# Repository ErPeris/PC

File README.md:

# Driver per 3 servomotori: progetto KiCad, due varianti

> Nel repository c'è anche la **scheda di test con Arduino Nano** (progetto 3): è nella cartella [`Scheda_Test_Arduino/`](Scheda_Test_Arduino/README.md), che ha il suo README.

Il circuito prende l'alimentazione da una batteria LiPo 2S (7.4 V), la abbassa a 5 V per i servo e porta i tre segnali PWM del microcontrollore da 3.3 V a livello 5 V con un LM324. Tutti i componenti sono a foro passante (THT).

| Cartella | Regolatore | File |
|---|---|---|
| `Variante_A_LDO/` | lineare LM7805 (TO-220) + diodo di protezione 1N4007 | schema `Servo_Driver_A_LDO.kicad_sch`, PCB `Servo_Driver_A_LDO.kicad_pcb`, anteprime `Servo_Driver_A_LDO.pdf` e `Servo_Driver_A_LDO_PCB.pdf` |
| `Variante_B_Buck/` | switching LM2596T-5.0 (TO-220-5) con componenti discreti | schema `Servo_Driver_B_Buck.kicad_sch`, PCB `Servo_Driver_B_Buck.kicad_pcb`, anteprime `Servo_Driver_B_Buck.pdf` e `Servo_Driver_B_Buck_PCB.pdf` |

Ogni cartella è un progetto KiCad autonomo: si apre con il file `.kicad_pro`. I file sono stati creati con KiCad 7 e si aprono in KiCad 9, che li converte al nuovo formato al primo salvataggio. Al primo salvataggio KiCad 9 può avvisare che il file viene aggiornato: va bene.

## Il PCB

- **Scheda**: 80 × 60 mm, 2 strati, 4 fori di fissaggio M3 negli angoli.
- **Massa**: un piano di massa (GND) su entrambe le facce collega tutti i pin di massa.
- **Piste di potenza**: +BATT, +5V verso i servo e, nella variante B, il nodo di commutazione SW sono tracciate a mano, larghe 1.5 mm.
- **Segnali**: sbrogliati con l'autorouter Freerouting. Le piste sono larghe 0.4 mm e il resto della +5V 0.8 mm, con distanze minime di 0.3 mm.
- **Classi di net**: sono nel `.kicad_pro`. La classe `Power` comprende GND, +BATT, +5V e SW.
- **Disposizione**:
  - in alto, la batteria (J1) a sinistra e lo stadio di alimentazione;
  - in basso a sinistra, l'ingresso PWM (J2) con le resistenze;
  - al centro, l'LM324 su zoccolo DIP-14;
  - a destra, le tre uscite servo (J3–J5).
- **Serigrafia**: polarità della batteria (+/−), pin del connettore PWM (G, 1, 2, 3) e pin di ogni servo (G, +, S).
- **DRC**: senza errori e senza pad scollegati.

Il file `.kicad_dru` contiene una sola regola: accetta un solo raggio di collegamento termico per faccia, perché i pad di massa sono collegati al piano su tutte e due le facce. Senza questa regola il DRC segnala un pad di R5.

**Prima di mandare la scheda in produzione:**
1. In KiCad 9 lanciare il controllo regole elettriche (ERC) sullo schema e il controllo regole di progettazione (DRC) sul PCB, con la verifica di coerenza tra schema e PCB attiva.
2. Controllare le impronte di L1 e dei condensatori elettrolitici sui componenti acquistati (diametro e passo dei piedini).
3. Nella variante A lasciare spazio al dissipatore dietro la linguetta di U1, verso il bordo superiore.
4. Se il PCB è stato modificato, rigenerare i Gerber (vedi sotto).

Per modificare il PCB a mano conviene ricaricare le zone di massa con il tasto **B** dopo ogni modifica.

## File per ordinare le schede

Nella cartella `produzione/` ci sono:

| File | Contenuto |
|---|---|
| `Gerber_Servo_Driver_A_LDO.zip` | Gerber e forature della variante A, da caricare così com'è sul sito del produttore |
| `Gerber_Servo_Driver_B_Buck.zip` | Gerber e forature della variante B |
| `Progetto_KiCad_Driver_3_Servo.zip` | progetto KiCad completo delle due varianti (schemi, PCB, regole, PDF, Gerber, README) |
| `Gerber_Scheda_Test_Arduino.zip` | Gerber e forature della scheda di test con Arduino Nano |
| `Progetto_KiCad_Scheda_Test_Arduino.zip` | progetto KiCad completo della scheda di test, con lo sketch di prova |

Ogni zip Gerber contiene:
- rame lato componenti e lato saldature (`.gtl`, `.gbl`);
- maschera di saldatura (`.gts`, `.gbs`);
- serigrafia (`.gto`, `.gbo`);
- contorno della scheda (`.gm1`);
- forature metallizzate e non metallizzate (`-PTH.drl`, `-NPTH.drl`, Excellon in mm);
- il file di job (`.gbrjob`).

**Dati da inserire nell'ordine** (JLCPCB, PCBWay e simili):

| Parametro | Valore |
|---|---|
| Strati | 2 |
| Dimensioni | 80 × 60 mm |
| Spessore | 1.6 mm |
| Rame | 1 oz |
| Pista minima / distanza minima | 0.4 mm / 0.3 mm |
| Foro minimo | 0.4 mm (via) |
| Finitura | HASL |
| Colore | a piacere |

Questi valori rientrano nelle opzioni standard di tutti i produttori economici.

**Per rigenerare i Gerber dopo una modifica**, in KiCad 9 dall'editor PCB:
1. Usare **File → Fabbricazione → Gerber**. Strati da includere: F.Cu, B.Cu, F.Silkscreen, B.Silkscreen, F.Mask, B.Mask, Edge.Cuts.
2. Nella stessa finestra usare **Genera file di foratura**: Excellon, millimetri, PTH e NPTH separati.
3. Comprimere i file in uno zip.

Da riga di comando:

```sh
kicad-cli pcb export gerbers -o gerber/ --layers F.Cu,B.Cu,F.SilkS,B.SilkS,F.Mask,B.Mask,Edge.Cuts \
    --exclude-value --subtract-soldermask Servo_Driver_A_LDO.kicad_pcb
kicad-cli pcb export drill -o gerber/ --format excellon --excellon-units mm --excellon-separate-th \
    Servo_Driver_A_LDO.kicad_pcb
```

## Parte comune alle due varianti

| Rif. | Valore | Impronta | Funzione |
|---|---|---|---|
| J1 | JST-PH 2 pin | `JST_PH_B2B-PH-K_1x02_P2.00mm_Vertical` | ingresso batteria (1 = +, 2 = GND) |
| C1 | 100 µF 16 V elettrolitico | `CP_Radial_D6.3mm_P2.50mm` | filtro in parallelo all'ingresso |
| J2 | header 1x4 2.54 mm | `PinHeader_1x04_P2.54mm_Vertical` | dal microcontrollore: 1 = GND, 2/3/4 = PWM1/2/3 a 3.3 V |
| U2 | LM324 | `DIP-14_W7.62mm` | 3 comparatori (U2A, U2B, U2C) come level shifter |
| R1 | 22 kΩ | `R_Axial_DIN0207…` | partitore di riferimento (lato +5 V) |
| R2 | 10 kΩ | `R_Axial_DIN0207…` | partitore di riferimento (lato GND) |
| C2 | 100 nF | `C_Disc_D5.0mm…` | filtro sulla tensione di riferimento VREF |
| R3, R4, R5 | 100 kΩ | `R_Axial_DIN0207…` | pull-down sugli ingressi PWM |
| C3 | 100 nF | `C_Disc_D5.0mm…` | disaccoppiamento alimentazione LM324 (vicino al pin 4) |
| J3, J4, J5 | header 1x3 2.54 mm | `PinHeader_1x03_P2.54mm_Vertical` | uscite servo: 1 = GND, 2 = +5 V, 3 = PWM 5 V |
| H1–H4 | foro M3 | `MountingHole_3.2mm_M3` | fissaggio della scheda |

**Come funziona il level shifter.** Il partitore R1/R2 genera VREF = 5 V × 10k / (22k + 10k) ≈ 1.56 V, collegata agli ingressi invertenti (−) di U2A, U2B e U2C. Ogni PWM a 3.3 V entra nell'ingresso non invertente (+). Con il PWM a 3.3 V (sopra la soglia) l'uscita va alta, con il PWM a 0 V va bassa. La quarta sezione, U2D, non è usata: è collegata come inseguitore con IN+ a massa, così non oscilla.

## Variante A: regolatore lineare LDO

| Rif. | Valore | Impronta | Funzione |
|---|---|---|---|
| U1 | LM7805 | `TO-220-3_Vertical` | regolatore 5 V (1 = IN, 2 = GND, 3 = OUT) |
| D1 | 1N4007 | `D_DO-41_SOD81_P10.16mm_Horizontal` | antiparallelo: catodo su IN, anodo su OUT |
| C4 | 330 nF | `C_Disc_D5.0mm…` | condensatore d'ingresso consigliato dal datasheet del 7805 |
| C5 | 100 nF | `C_Disc_D5.0mm…` | condensatore d'uscita consigliato dal datasheet |
| C6 | 100 µF 10 V elettrolitico | `CP_Radial_D6.3mm_P2.50mm` | riserva per i picchi di corrente dei servo |

## Variante B: buck converter LM2596-5.0

| Rif. | Valore | Impronta | Funzione |
|---|---|---|---|
| U1 | LM2596T-5.0 | `TO-220-5_P3.4x3.7mm_StaggerOdd_Lead3.8mm_Vertical` | 1 = VIN, 2 = OUT, 3 = GND, 4 = FEEDBACK, 5 = ON/OFF |
| C4 | 100 µF 16 V elettrolitico | `CP_Radial_D8.0mm_P3.50mm` | condensatore d'ingresso sul pin VIN |
| D1 | 1N5822 (Schottky 3 A) | `D_DO-201AD_P15.24mm_Horizontal` | tra OUT (catodo) e GND (anodo) |
| L1 | 33 µH, ≥ 3 A | `L_Radial_D12.0mm_P5.00mm_Fastron_11P` | induttore sulla linea d'uscita |
| C5 | 220 µF 10 V low-ESR | `CP_Radial_D8.0mm_P3.50mm` | condensatore d'uscita sui 5 V |

La specifica chiede l'**LM2596S**-5.0, che esiste solo in contenitore SMD (TO-263). Visto che la scheda è tutta a foro passante, ho usato l'**LM2596T**-5.0: è lo stesso integrato in contenitore TO-220-5, con gli stessi pin. Va comprata la versione con i piedini sfalsati per il montaggio verticale. Se il professore vuole proprio la versione "S", basta cambiare simbolo e impronta di U1.

Il pin FEEDBACK (4) è collegato ai 5 V dopo l'induttore. Sul PCB la pista passa sul lato inferiore fino al pin 2 di L1. Il pin ON/OFF (5) va a GND, altrimenti il regolatore resta spento: la specifica non lo nomina, ma è necessario.

## Cose da sapere (da riportare anche nella relazione)

1. **L'LM324 a 5 V non arriva a 5 V in uscita.** Non è rail-to-rail: con alimentazione a 5 V l'uscita alta arriva a circa 3.5–3.8 V. Ai servo basta (accettano già segnali da 3.3 V), ma non sono 5 V pieni. Per averli si può montare un **MCP6004** o un **LMV324** nello stesso zoccolo DIP-14: hanno lo stesso pinout, quindi schema e PCB non cambiano.
2. **LM7805 e batteria 2S.** Il 7805 ha bisogno di circa 2 V di margine, quindi sotto ~7 V di batteria l'uscita scende sotto 5 V, e una LiPo 2S va da 8.4 V (carica) a ~6.4 V (scarica). L'**LM2940-5.0** ha lo stesso pinout TO-220 e un dropout di circa 0.5 V.
3. **Calore nella variante A.** Il regolatore lineare dissipa (Vin − 5 V) × I: con 7.4 V e 1 A sono circa 2.4 W, quindi serve un dissipatore sul TO-220. Il 7805 eroga al massimo ~1.5 A. Tre servo che si muovono insieme possono superarlo (ogni SG90 in stallo assorbe ~0.7 A, i servo più grandi anche 2 A). La variante B arriva a 3 A con molto meno calore.
4. **Layout della variante B.** L'anello C4 → U1 → D1 → L1 → C5 è tenuto corto, con il piano di massa sotto. L'impronta di L1 è indicativa: va controllata sul componente acquistato.
5. **Polarità della batteria.** Su J1 il pin 1 è il + e il pin 2 è la massa, come indicato sulla serigrafia. I connettori JST-PH delle LiPo non hanno tutti la stessa polarità: va controllata prima del primo collegamento. Non è prevista una protezione contro l'inversione di polarità.
6. **Aggiunte rispetto alla specifica.** R3–R5 (pull-down), C2 (filtro di VREF), C3 (disaccoppiamento), i fori di fissaggio e, nella variante A, C4–C6 non sono richiesti dalla specifica. Sono pratica comune e si possono togliere senza cambiare il funzionamento base.

## Rigenerare i file

Gli schemi e i PCB sono stati generati dagli script in `tools/`, che servono solo a ricrearli da zero. Per modificarli basta lavorare direttamente in KiCad. Rigenerando, le modifiche fatte a mano vanno perse.

```sh
python3 tools/genera_schemi.py      # schemi (.kicad_sch)
kicad-cli sch export netlist --format kicadxml -o A.xml Variante_A_LDO/Servo_Driver_A_LDO.kicad_sch
python3 tools/verifica_netlist.py A A.xml   # confronta i collegamenti con la specifica
FREEROUTING_JAR=freerouting-2.4.1-executable.jar JAVA=java-25 python3 tools/genera_pcb.py   # PCB
```

`genera_pcb.py` usa il modulo Python `pcbnew` di KiCad 7 e [Freerouting](https://freerouting.app) 2.4.1, che richiede Java 25.

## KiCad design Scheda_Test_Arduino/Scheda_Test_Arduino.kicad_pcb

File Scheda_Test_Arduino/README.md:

# Scheda di test con Arduino Nano

Scheda con un Arduino Nano come controllo, collegato a:
- un modulo BME280 (temperatura, umidità, pressione);
- un buzzer;
- un servomotore.

Un interruttore accende tutta la scheda e un LED si accende quando l'interruttore è su ON. Tutti i componenti sono a foro passante.

| File | Contenuto |
|---|---|
| `Scheda_Test_Arduino.kicad_pro` | progetto KiCad da aprire |
| `Scheda_Test_Arduino.kicad_sch` / `.pdf` | schema |
| `Scheda_Test_Arduino.kicad_pcb` / `_PCB.pdf` | circuito stampato |
| `gerber/` | Gerber e forature per ordinare la scheda |
| `firmware/test_scheda/test_scheda.ino` | sketch di prova |

Come per il driver servo, i file sono in formato KiCad 7 e si aprono in KiCad 9.

## Come funziona

- **Alimentazione:** la batteria (7–12 V, per esempio la stessa LiPo 2S da 7.4 V) entra dal connettore JST J1. Passa dall'interruttore SW1 e arriva al pin VIN dell'Arduino. Il regolatore dell'Arduino genera i 5 V per servo e buzzer e i 3.3 V per il sensore. C1 filtra la tensione dopo l'interruttore.
- **LED di accensione:** D1 con R1 da 1 kΩ è collegato dopo l'interruttore, quindi si accende solo con l'interruttore su ON. Assorbe circa 5 mA a 7.4 V.
- **BME280:** si collega via I2C con SDA su A4 e SCL su A5. È alimentato a 3.3 V, che va bene sia per i moduli solo 3.3 V sia per quelli con regolatore a 5 V.
- **Servo:** il segnale arriva da D9, l'alimentazione dai 5 V dell'Arduino. C2 da 220 µF assorbe i picchi di corrente del motore.
- **Buzzer:** è pilotato da D8 tramite il transistor Q1 (BC547), perché un buzzer può assorbire più corrente di quella che un pin dell'Arduino regge bene.
  - R2 limita la corrente di base.
  - R3 tiene il transistor spento durante il reset.
  - D2 protegge Q1 dalle sovratensioni dei buzzer magnetici.

  Funziona sia con buzzer attivi sia passivi da 5 V.

| Pin Arduino | Collegato a |
|---|---|
| VIN | batteria dopo l'interruttore |
| 5V | servo (+), buzzer (+) |
| 3V3 | BME280 VCC |
| A4 / A5 | BME280 SDA / SCL |
| D8 | buzzer (base di Q1 tramite R2) |
| D9 | segnale del servo |

## Componenti

| Rif. | Valore | Impronta | Note |
|---|---|---|---|
| U1 | Arduino Nano | `Module:Arduino_Nano` | montato su due strip femmina 1x15, con la USB verso il bordo |
| J1 | JST-PH 2 pin | `JST_PH_B2B-PH-K_1x02_P2.00mm_Vertical` | batteria: 1 = +, 2 = GND |
| SW1 | interruttore a slitta SPDT | `SW_Slide_SPDT_Straight_CK_OS102011MS2Q` | 3 pin a passo 2 mm |
| D1 | LED rosso 5 mm | `LED_D5.0mm` | spia di accensione |
| R1 | 1 kΩ | `R_Axial_DIN0207…` | resistenza del LED |
| C1 | 100 µF 16 V elettrolitico | `CP_Radial_D6.3mm_P2.50mm` | filtro dopo l'interruttore |
| J2 | strip femmina 1x4 | `PinSocket_1x04_P2.54mm_Vertical` | BME280: 1 = VCC, 2 = GND, 3 = SCL, 4 = SDA |
| J3 | strip maschio 1x3 | `PinHeader_1x03_P2.54mm_Vertical` | servo: 1 = GND, 2 = +5 V, 3 = segnale |
| C2 | 220 µF 10 V elettrolitico | `CP_Radial_D8.0mm_P3.50mm` | riserva per il servo |
| BZ1 | buzzer 5 V Ø12 mm | `Buzzer_12x9.5RM7.6` | piedini a passo 7.6 mm |
| Q1 | BC547 | `TO-92_Inline_Wide` | piedini a passo 2.54 mm, più facili da saldare |
| R2 | 1 kΩ | `R_Axial_DIN0207…` | base di Q1 |
| R3 | 10 kΩ | `R_Axial_DIN0207…` | tiene Q1 spento durante il reset |
| D2 | 1N4148 | `D_DO-35_SOD27_P7.62mm_Horizontal` | diodo di protezione sul buzzer |
| H1–H4 | foro M3 | `MountingHole_3.2mm_M3` | fissaggio |

## Il PCB

- **Scheda:** 80 × 58 mm, 2 strati, 4 fori M3 negli angoli.
- **Massa:** un piano di rame su tutte e due le facce.
- **Piste:** le alimentazioni (batteria, VIN, +5V) sono larghe 0.8 mm, i segnali 0.4 mm.
- **Disposizione:**
  - a sinistra, batteria, interruttore e LED;
  - al centro, l'Arduino, con la USB raggiungibile dal bordo destro;
  - in alto, lo zoccolo del BME280;
  - in basso, buzzer, transistor e connettore del servo.
- **Serigrafia:** polarità della batteria, nomi dei pin del BME280 (3V3, GND, SCL, SDA) e del servo (G, +, S).

Il DRC è pulito: 0 errori, 0 pad scollegati. Ho controllato i Gerber con un visualizzatore.

**Dati per l'ordine:**

| Parametro | Valore |
|---|---|
| Strati | 2 |
| Dimensioni | 80 × 58 mm |
| Spessore | 1.6 mm |
| Rame | 1 oz |
| Finitura | HASL |
| Pista minima | 0.4 mm |
| Distanza minima | 0.2 mm |
| Foro minimo | 0.75 mm |

La distanza minima è 0.2 mm invece di 0.3 mm per un solo motivo: nell'impronta dell'interruttore le linguette di fissaggio distano 0.25 mm dai pin. È comunque ampiamente nei limiti dei produttori economici, che arrivano a 0.1 mm.

## Cose da sapere

1. **Corrente del servo.** Il servo prende i 5 V dal regolatore dell'Arduino, che regge circa 0.5 A. Va bene un micro servo (SG90, MG90S). Un servo più grande va alimentato a parte, per esempio con il driver del progetto 1.
2. **Interruttore.** Molti interruttori a slitta piccoli sono dati per 0.1–0.5 A. Conviene sceglierne uno da almeno 0.5 A, con 3 pin a passo 2 mm.
3. **Ordine dei pin del BME280.** Lo zoccolo J2 segue l'ordine più comune dei moduli GY-BME280 a 4 pin: VCC, GND, SCL, SDA. Va controllato sul proprio modulo. I moduli a 6 pin (VCC, GND, SCL, SDA, CSB, SDO) entrano con i primi 4 pin, lasciando fuori CSB e SDO.
4. **Livelli I2C.** Il modulo porta SDA e SCL a 3.3 V, che l'Arduino a 5 V legge come livello alto. È il collegamento usato normalmente con questi moduli.
5. **USB.** Con il cavo USB collegato l'Arduino resta acceso anche con l'interruttore su OFF. Il LED invece resta spento, perché è sul lato batteria.
6. **Batteria.** Non c'è protezione contro l'inversione di polarità: va controllata la polarità del connettore prima di collegarlo (pin 1 = +, come indicato sulla serigrafia).

## Sketch di prova

`firmware/test_scheda/test_scheda.ino` fa tre cose:
- all'accensione suona un beep;
- ogni ciclo stampa temperatura, umidità e pressione sul monitor seriale (9600 baud);
- muove il servo tra 0°, 90° e 180°.

Richiede la libreria **Adafruit BME280 Library** (dal gestore librerie dell'IDE). La libreria Servo è già inclusa nell'IDE.

L'ho compilato per Arduino Nano (ATmega328) senza errori né avvisi. Non avendo qui le librerie Servo e Adafruit, ho usato interfacce con le stesse firme: va ricompilato una volta nell'IDE con le librerie vere.

## Rigenerare i file

```sh
FREEROUTING_JAR=freerouting-2.4.1-executable.jar JAVA=java-25 python3 tools/genera_scheda_arduino.py
```

Lo script si lancia dalla cartella principale del repository. Rigenerando, le modifiche fatte a mano in KiCad vanno perse.

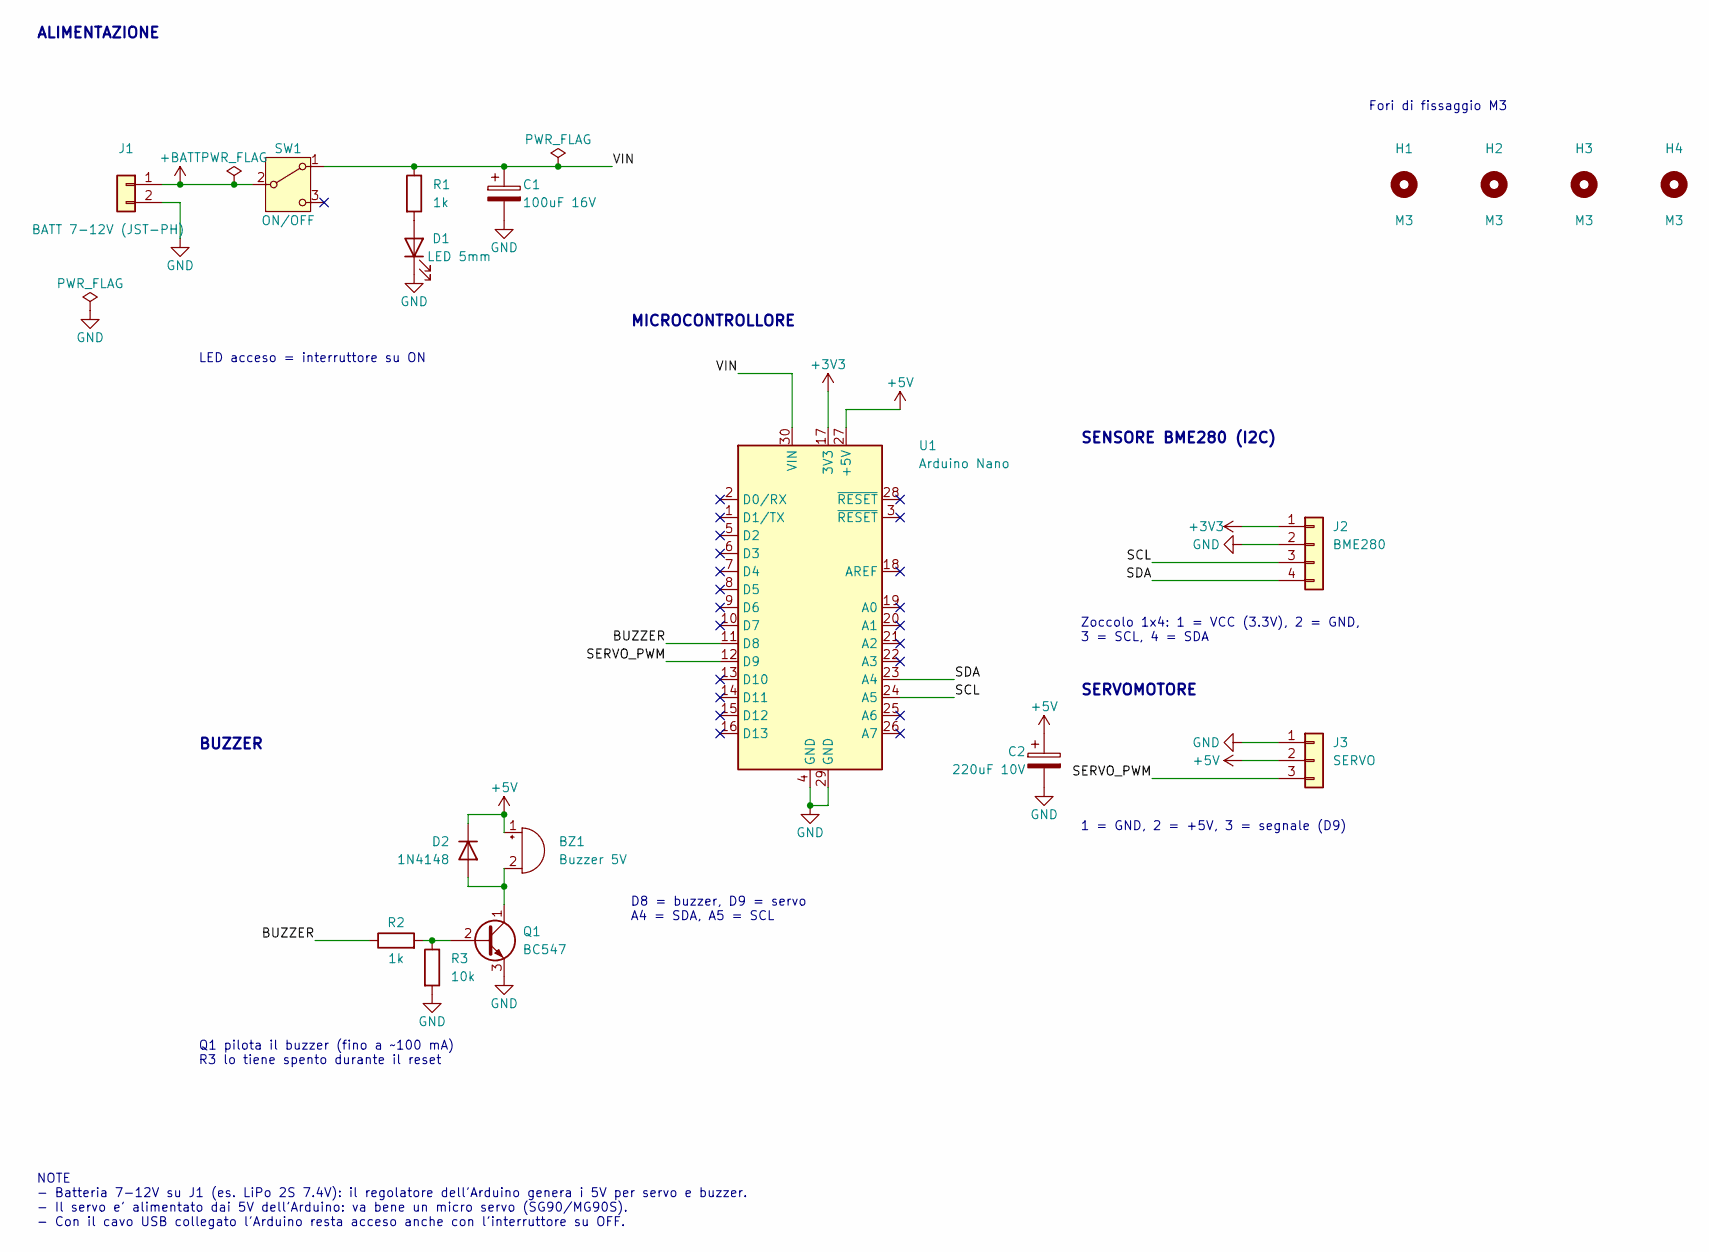
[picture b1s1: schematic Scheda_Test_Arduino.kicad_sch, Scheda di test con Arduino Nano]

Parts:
BZ1: Buzzer 5V; Buzzer_12x9.5RM7.6
C1: 100uF 16V; CP_Radial_D6.3mm_P2.50mm
C2: 220uF 10V; CP_Radial_D8.0mm_P3.50mm
D1: LED 5mm; LED_D5.0mm
D2: 1N4148; D_DO-35_SOD27_P7.62mm_Horizontal
H1, H2, H3, H4: M3; MountingHole_3.2mm_M3
J1: BATT 7-12V (JST-PH); JST_PH_B2B-PH-K_1x02_P2.00mm_Vertical
J2: BME280; PinSocket_1x04_P2.54mm_Vertical
J3: SERVO; PinHeader_1x03_P2.54mm_Vertical
Q1: BC547; TO-92_Inline_Wide
R1, R2: 1k; R_Axial_DIN0207_L6.3mm_D2.5mm_P10.16mm_Horizontal
R3: 10k; R_Axial_DIN0207_L6.3mm_D2.5mm_P10.16mm_Horizontal
SW1: ON/OFF; SW_Slide_SPDT_Straight_CK_OS102011MS2Q
U1: Arduino Nano; Arduino_Nano

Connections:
+3V3: J2.1, U1.17 (3V3)
+5V: BZ1.1 (+), C2.1, D2.1 (K), J3.2, U1.27 (+5V)
+BATT: J1.1, SW1.2 (B)
/BUZZER: R2.1, U1.11 (D8)
/SCL: J2.3, U1.24 (A5)
/SDA: J2.4, U1.23 (A4)
/SERVO_PWM: J3.3, U1.12 (D9)
/VIN: C1.1, R1.1, SW1.1 (A), U1.30 (VIN)
GND: C1.2, C2.2, D1.1 (K), J1.2, J2.2, J3.1, Q1.3 (E), R3.2, U1.4 (GND), U1.29 (GND)
unnamed: BZ1.2 (-), D2.2 (A), Q1.1 (C)
unnamed: D1.2 (A), R1.2
unnamed: Q1.2 (B), R2.2, R3.1

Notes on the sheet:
ALIMENTAZIONE
LED acceso = interruttore su ON
MICROCONTROLLORE
D8 = buzzer, D9 = servo A4 = SDA, A5 = SCL
SENSORE BME280 (I2C)
Zoccolo 1x4: 1 = VCC (3.3V), 2 = GND, 3 = SCL, 4 = SDA
SERVOMOTORE
1 = GND, 2 = +5V, 3 = segnale (D9)
BUZZER
Q1 pilota il buzzer (fino a ~100 mA) R3 lo tiene spento durante il reset
Fori di fissaggio M3
NOTE - Batteria 7-12V su J1 (es. LiPo 2S 7.4V): il regolatore dell'Arduino genera i 5V per servo e buzzer. - Il servo e' alimentato dai 5V dell'Arduino: va bene un micro servo (SG90/MG90S). - Con il cavo USB collegato l'Arduino resta acceso anche con l'interruttore su OFF.

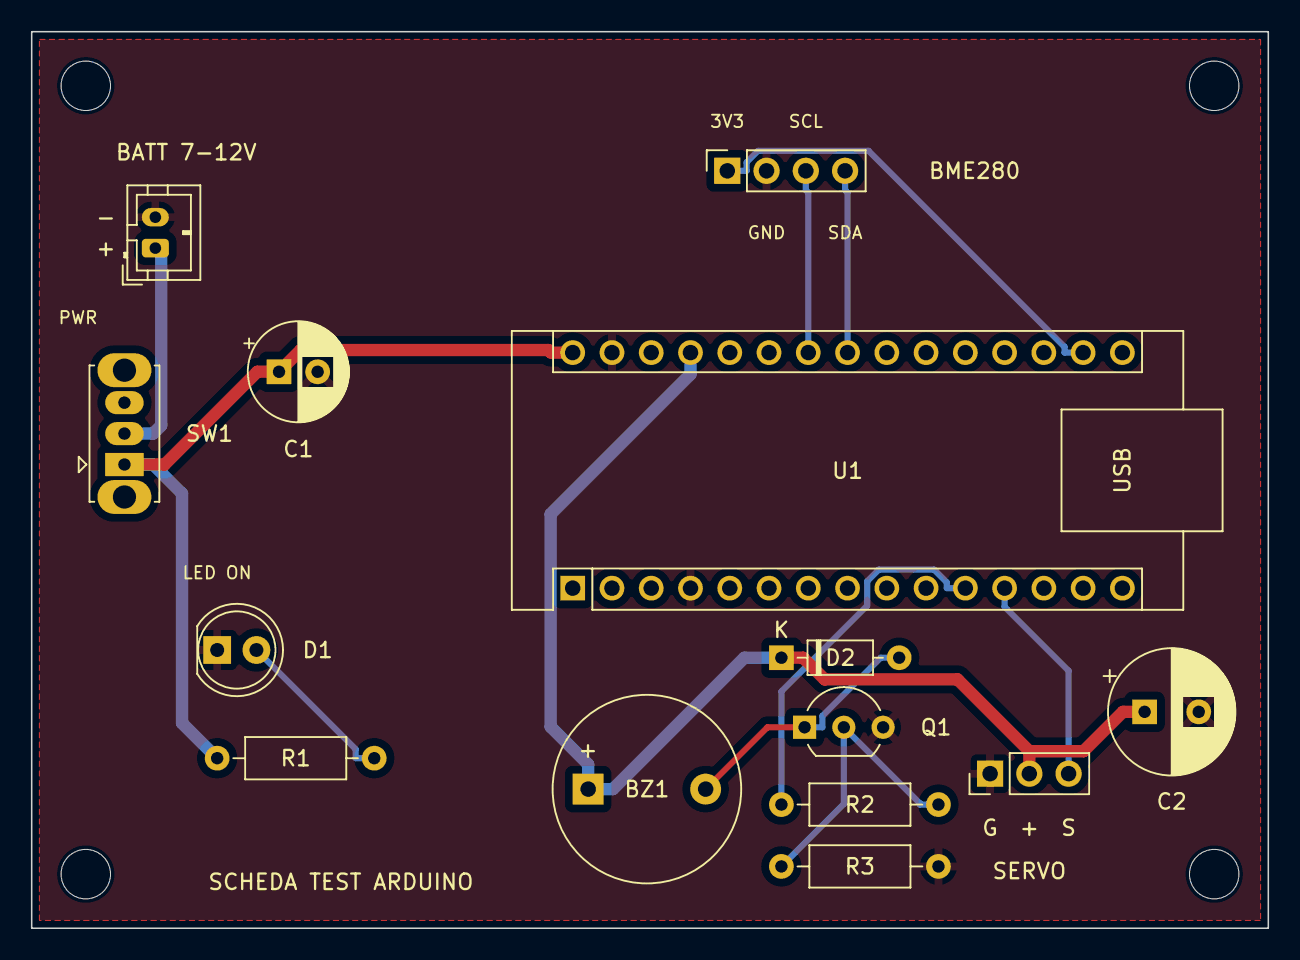
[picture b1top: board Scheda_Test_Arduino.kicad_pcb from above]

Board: 2 copper layers, 80.0 x 58.0 mm, 18 parts (0 on the bottom side), 12 nets.

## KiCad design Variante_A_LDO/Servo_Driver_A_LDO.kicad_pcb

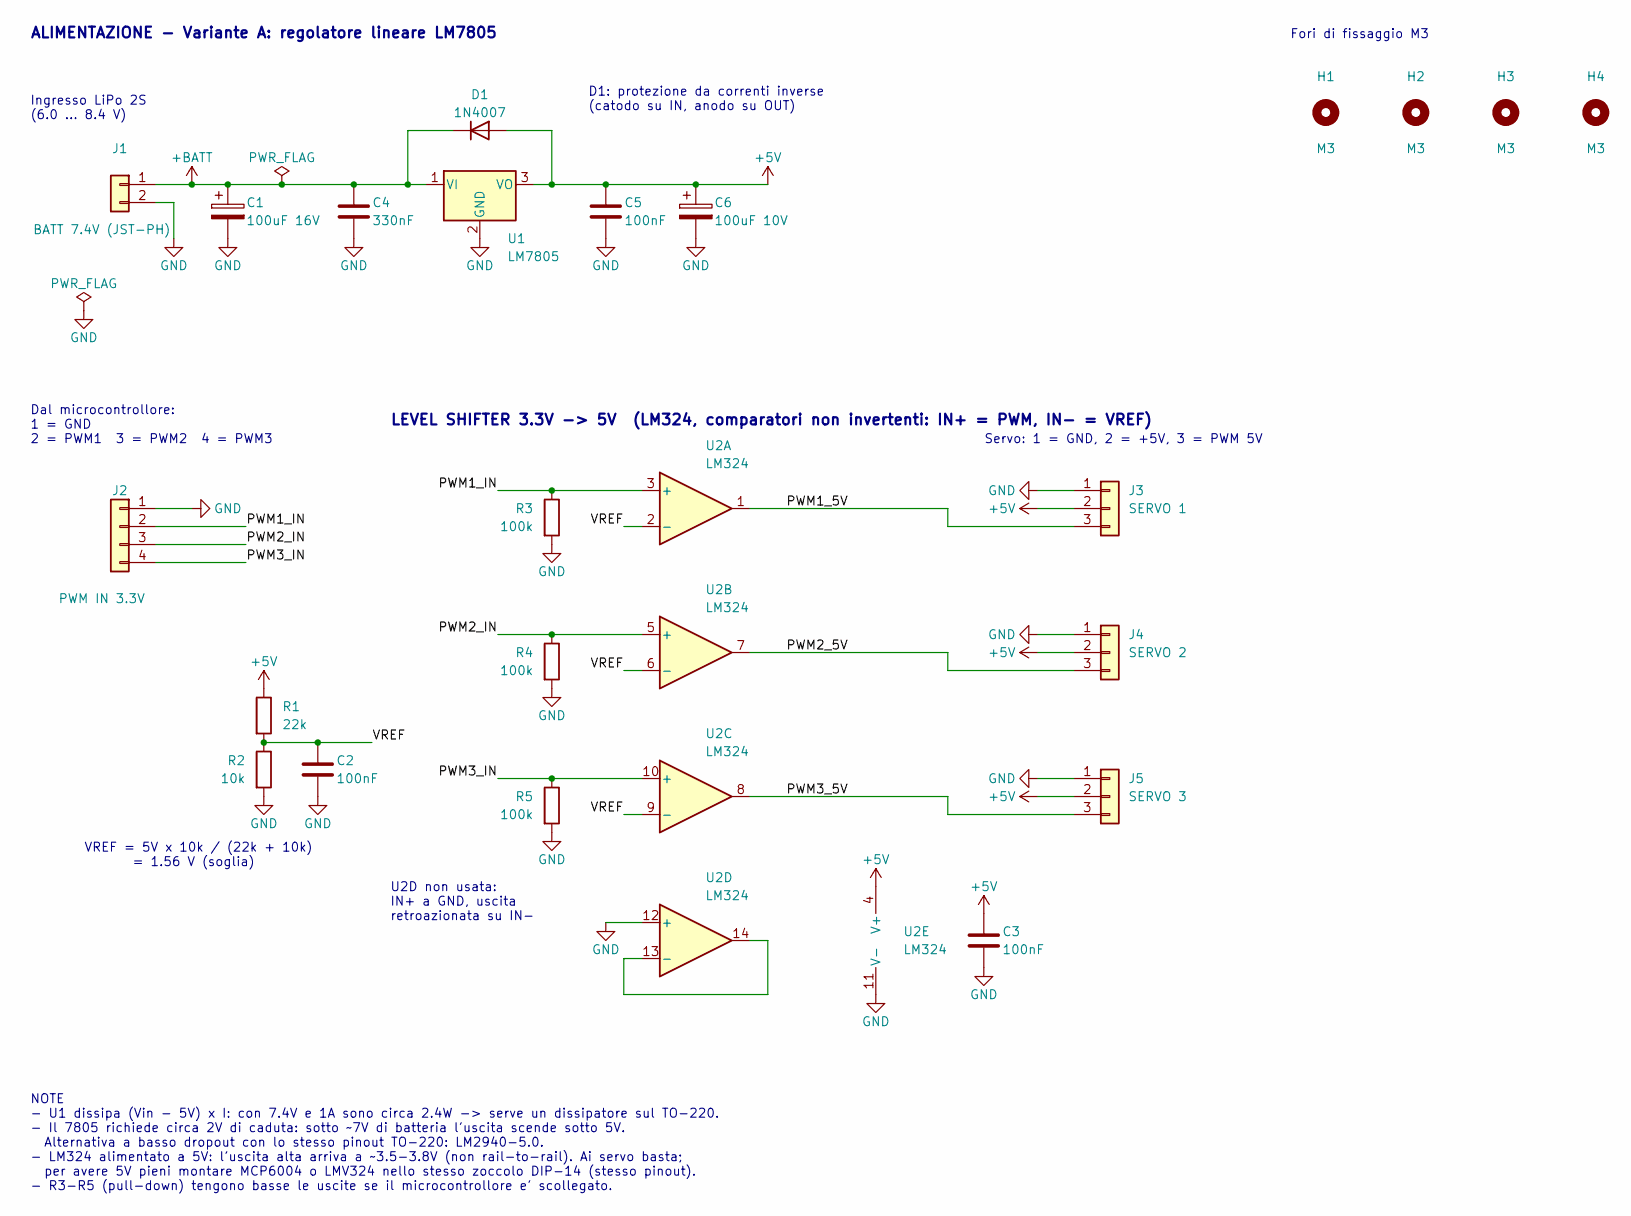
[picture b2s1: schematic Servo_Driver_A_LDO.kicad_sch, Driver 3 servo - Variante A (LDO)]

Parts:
C1: 100uF 16V; CP_Radial_D6.3mm_P2.50mm
C2, C3, C5: 100nF; C_Disc_D5.0mm_W2.5mm_P5.00mm
C4: 330nF; C_Disc_D5.0mm_W2.5mm_P5.00mm
C6: 100uF 10V; CP_Radial_D6.3mm_P2.50mm
D1: 1N4007; D_DO-41_SOD81_P10.16mm_Horizontal
H1, H2, H3, H4: M3; MountingHole_3.2mm_M3
J1: BATT 7.4V (JST-PH); JST_PH_B2B-PH-K_1x02_P2.00mm_Vertical
J2: PWM IN 3.3V; PinHeader_1x04_P2.54mm_Vertical
J3: SERVO 1; PinHeader_1x03_P2.54mm_Vertical
J4: SERVO 2; PinHeader_1x03_P2.54mm_Vertical
J5: SERVO 3; PinHeader_1x03_P2.54mm_Vertical
R1: 22k; R_Axial_DIN0207_L6.3mm_D2.5mm_P10.16mm_Horizontal
R2: 10k; R_Axial_DIN0207_L6.3mm_D2.5mm_P10.16mm_Horizontal
R3, R4, R5: 100k; R_Axial_DIN0207_L6.3mm_D2.5mm_P10.16mm_Horizontal
U1: LM7805; TO-220-3_Vertical
U2: LM324; DIP-14_W7.62mm

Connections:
+5V: C3.1, C5.1, C6.1, D1.2 (A), J3.2, J4.2, J5.2, R1.1, U1.3 (VO), U2.4 (V+)
+BATT: C1.1, C4.1, D1.1 (K), J1.1, U1.1 (VI)
/PWM1_5V: J3.3, U2.1
/PWM1_IN: J2.2, R3.1, U2.3 (+)
/PWM2_5V: J4.3, U2.7
/PWM2_IN: J2.3, R4.1, U2.5 (+)
/PWM3_5V: J5.3, U2.8
/PWM3_IN: J2.4, R5.1, U2.10 (+)
/VREF: C2.1, R1.2, R2.1, U2.2 (-), U2.6 (-), U2.9 (-)
GND: C1.2, C2.2, C3.2, C4.2, C5.2, C6.2, J1.2, J2.1, J3.1, J4.1, J5.1, R2.2, R3.2, R4.2, R5.2, U1.2 (GND), U2.11 (V-), U2.12 (+)
unnamed: U2.13 (-), U2.14

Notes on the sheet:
ALIMENTAZIONE - Variante A: regolatore lineare LM7805
Ingresso LiPo 2S (6.0 ... 8.4 V)
D1: protezione da correnti inverse (catodo su IN, anodo su OUT)
Dal microcontrollore: 1 = GND 2 = PWM1 3 = PWM2 4 = PWM3
VREF = 5V x 10k / (22k + 10k) = 1.56 V (soglia)
Servo: 1 = GND, 2 = +5V, 3 = PWM 5V
U2D non usata: IN+ a GND, uscita retroazionata su IN-
Fori di fissaggio M3
LEVEL SHIFTER 3.3V -> 5V (LM324, comparatori non invertenti: IN+ = PWM, IN- = VREF)
NOTE - U1 dissipa (Vin - 5V) x I: con 7.4V e 1A sono circa 2.4W -> serve un dissipatore sul TO-220. - Il 7805 richiede circa 2V di caduta: sotto ~7V di batteria l'uscita scende sotto 5V. Alternativa a basso dropout con lo stesso pinout TO-220: LM2940-5.0. - LM324 alimentato a 5V: l'uscita alta arri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

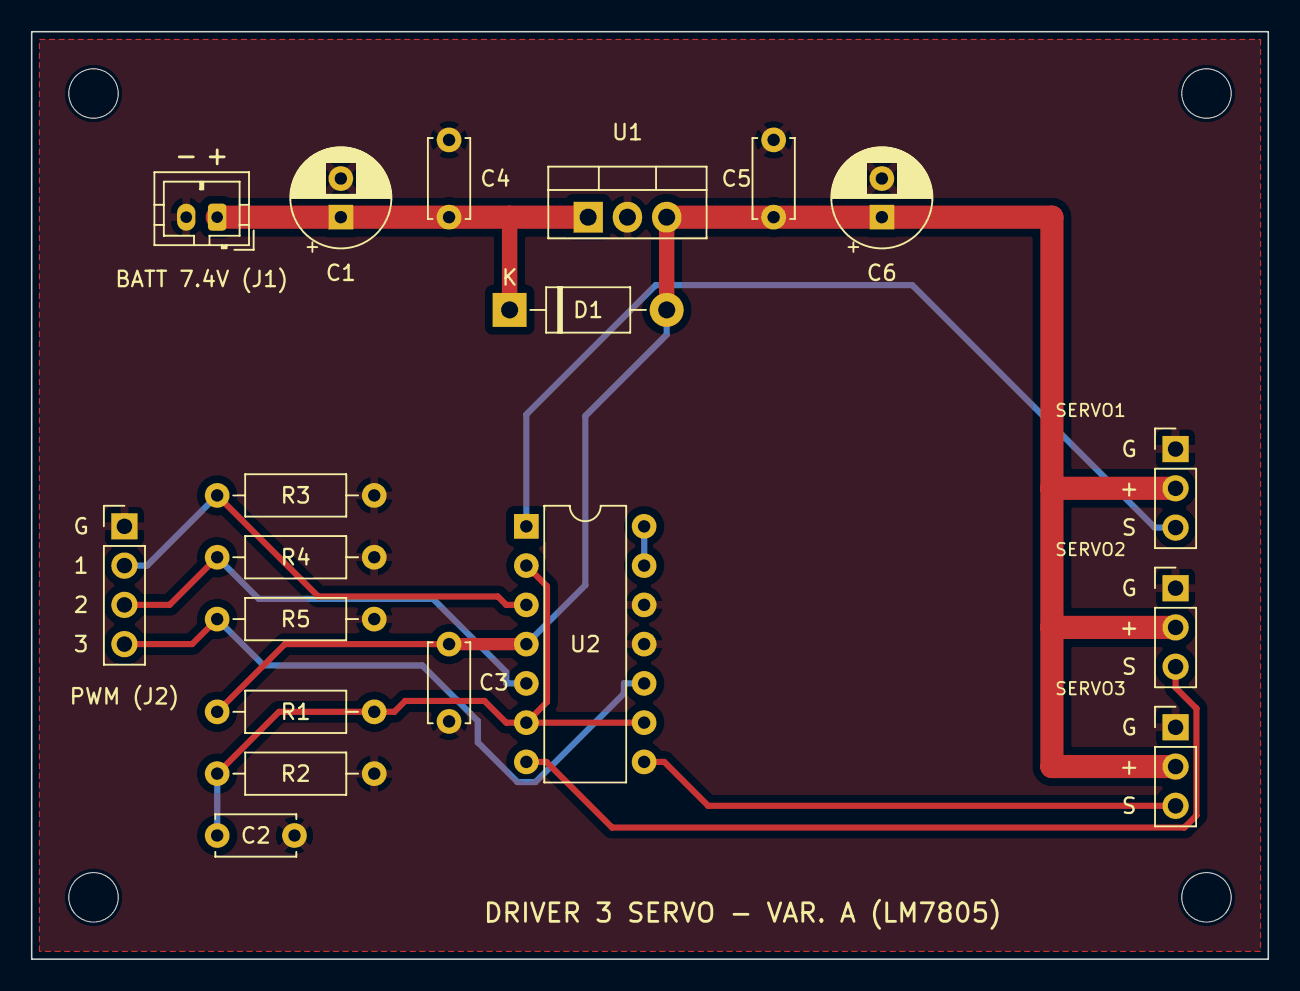
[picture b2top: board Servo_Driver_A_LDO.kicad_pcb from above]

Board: 2 copper layers, 80.0 x 60.0 mm, 23 parts (0 on the bottom side), 11 nets.
